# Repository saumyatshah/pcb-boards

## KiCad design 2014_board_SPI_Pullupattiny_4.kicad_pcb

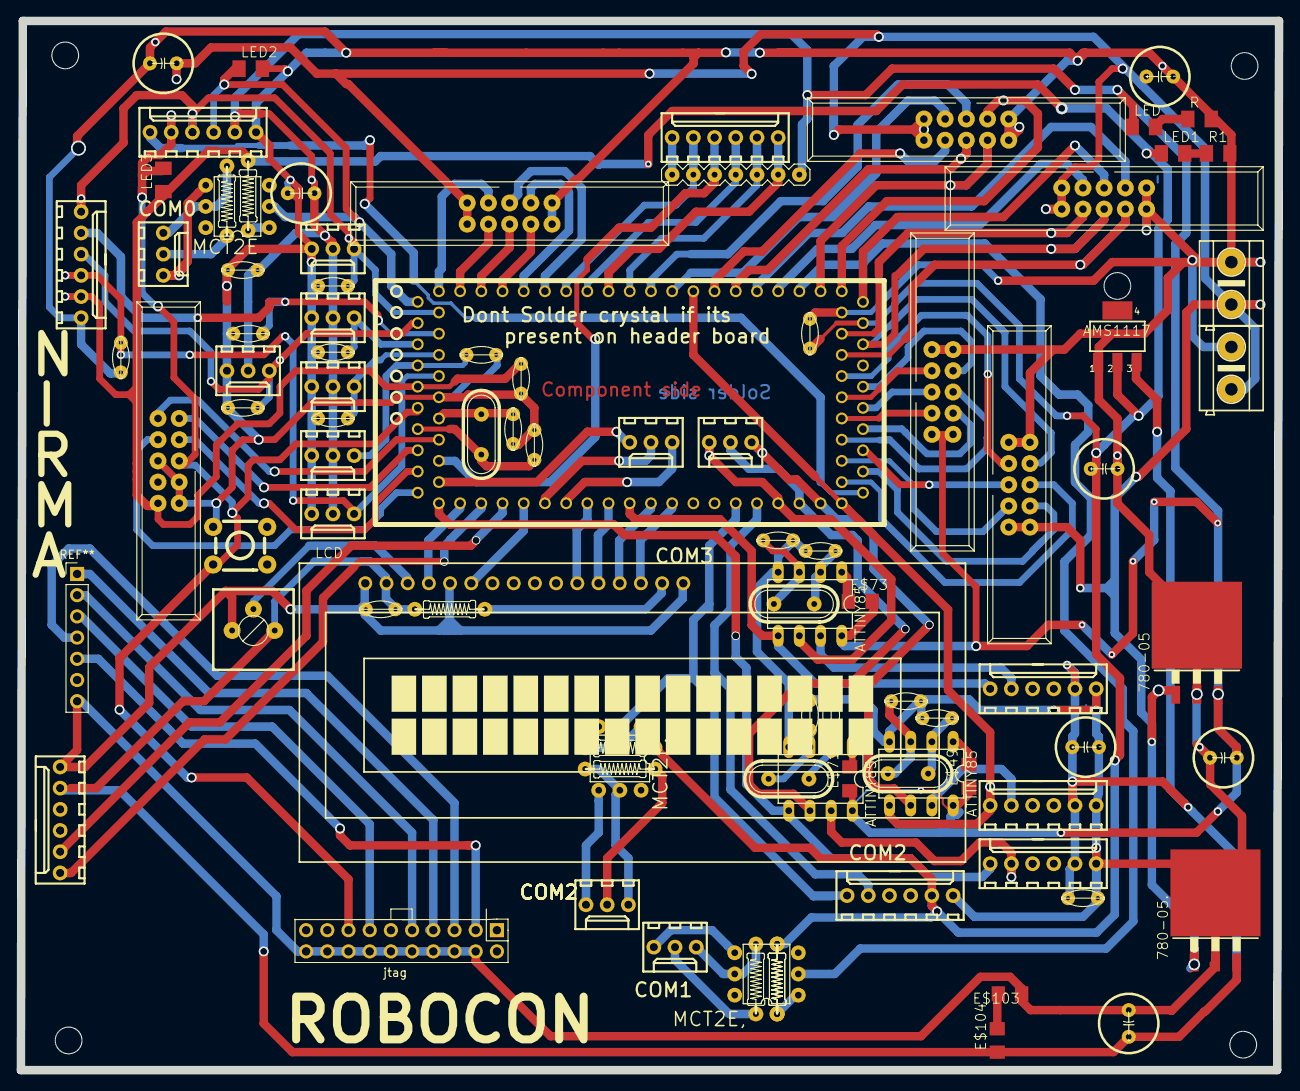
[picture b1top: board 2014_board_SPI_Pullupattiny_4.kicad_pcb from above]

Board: 2 copper layers, 150.7 x 125.7 mm, 97 parts (0 on the bottom side), 78 nets.

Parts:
780-05, 780-05.: TO263-3
@HOLE0, @HOLE1, @HOLE2, @HOLE3, @HOLE4: (no value)
AMS1117: SOT223
ATTINY85, ATTINY85,, ATTINY85.: DIL08
E$1: LPC1769-HEADER
E$2, E$18, E$27, E$30: CRYSTAL
E$3, E$4, E$5, E$6, E$15, E$19, E$20, E$25, E$26, E$28, E$29, E$31, E$51, E$57, E$61, E$62, E$66, E$67, E$85, E$86: CAPACITOR(CERAMIC)
E$7, E$8, E$8#2, E$56, E$64, E$65: FRC(10)
E$9, E$35, E$48, E$50, E$52, E$53, E$54, E$55, E$59, E$60, E$76: CONNECTOR(3_PIN)
E$13, E$34, E$36, E$69, E$70, E$74, E$75, E$95: RESISTER(HORIZONTAL)
E$21, E$22, E$23, E$32, E$37, E$83, E$84, E$106: CONNECTOR(6_PIN)
E$24, E$90, E$118, E$119, E$120, E$121, E$141: CAPACITOR(ELECTROLYTE_220)
E$38: POT(SQAURE)
E$49, E$71, E$73: R1206
E$63: SWITCH(PUSH-BUTTON)
E$103, E$104: C1206
E$108, E$109: CONNECTOR(GREEN)
E$113: RESISTER_ARRAY(7)
LCD: TUXGR_16X2_R2
LED, LED1, LED2, LED3: M1206
MCT2E, MCT2E,, MCT2E.: DIL6
R, R1: M1206
jtag: PinHeader_2x10_P2.54mm_Vertical

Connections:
3.3V: E$1.P$15, E$1.P$77, E$32.2, E$34.2, E$56.5, E$74.2, E$83.2, E$95.2, LED3.1
5V_PERIPHERALS: 780-05..3, E$13.1, E$15.2, E$21.2, E$22.2, E$23.2, E$37.2, E$37.7, E$37.8, E$37.13, E$38.3, E$104.1, E$121.+, LCD.2
5V_SHARP: ATTINY85.8, ATTINY85,.8, ATTINY85..8, E$8#2.1, E$8#2.10, E$49.1, E$50.2, E$52.2, E$53.2, E$54.2, E$55.2, E$59.2, E$71.1, E$73.2, E$84.2, E$113.7, E$120.+
12V: 780-05.1, 780-05..1, E$7.1, E$7.10, E$8.1, E$8.10, E$64.1, E$64.10, E$65.1, E$65.10, E$108.P$2, E$109.P$2, E$118.+, E$141.+
GND: 780-05.2, 780-05.TAB, 780-05..2, 780-05..TAB, AMS1117.1, ATTINY85.4, ATTINY85,.4, ATTINY85..4, E$1.P$1, E$1.P$40, E$3.1, E$4.2, E$5.1, E$6.2, E$7.5, E$7.6, E$8.5, E$8.6, E$8#2.5, E$8#2.6, E$15.1, E$19.1, E$20.2, E$21.1, E$22.1, E$23.1, E$24.-, E$25.2, E$26.1, E$28.2, E$29.2, E$31.1, E$32.1, E$37.1, E$38.1, E$50.1, E$52.1, E$53.1, E$54.1, E$55.1, E$56.3, E$56.6, E$56.7, E$57.1, E$59.1, E$63.SW1_, E$64.5, E$64.6, E$65.5, E$65.6, E$66.1, E$67.1, E$83.1, E$84.1, E$85.1, E$86.1, E$90.-, E$103.1, E$108.P$1, E$109.P$1, E$118.-, E$119.-, E$120.-, E$121.-, E$141.-, LCD.1, LCD.5, LCD.16, LED2.2, R.2, R1.2, jtag.4, jtag.6, jtag.8, jtag.10, jtag.12, jtag.14, jtag.16, jtag.18, jtag.20
S$2: ATTINY85..7, E$23.5
S$6: E$1.P$44, E$8#2.7
S$8: ATTINY85,.6, E$1.P$52, E$9.1
S$9: E$1.P$36, E$64.9
S$10: E$1.P$74, E$8#2.4
S$13: E$1.P$48, E$7.3
S$17: E$1.P$47, E$7.9
S$19: E$1.P$73, E$8#2.8
S$21: E$1.P$42, E$64.4
S$22: E$1.P$45, E$8#2.9
S$24: E$1.P$71, E$7.8
S$25: E$1.P$41, E$64.2
S$27: E$1.P$70, E$7.2
S$34: ATTINY85.5, E$1.P$32, E$1.P$49, E$22.6
S$36: E$35.2, E$36.2
S$41: E$76.3, MCT2E,.P$2
S$44: E$1.P$5, E$55.3, E$83.6, E$84.4
S$48: ATTINY85.7, E$22.5, E$22.11, E$22.17
S$51: ATTINY85,.7, E$21.5
S$52: ATTINY85..6, E$1.P$51, E$9.2
S$53: ATTINY85..5, E$1.P$68, E$23.6
S$54: ATTINY85.6, E$1.P$50, E$9.3
S$55: E$1.P$66, E$37.6, E$37.12, E$37.18
S$57: E$1.P$53, E$32.5
S$60: E$1.P$20, E$8.P$20
S$61: E$34.1, MCT2E..P$4
S$62: ATTINY85,.5, E$1.P$59, E$21.6
S$65: E$1.P$9, E$48.1
S$68: E$1.P$27, E$106.3, E$113.4
S$71: E$35.1, MCT2E..P$3
S$74: E$35.3, E$36.1, MCT2E..P$2
S$75: E$1.P$11, E$56.2
S$76: E$1.P$29, E$106.2, E$113.5
S$83: E$1.P$62, E$48.3
S$86: E$1.P$63, E$48.2
S$88: E$1.P$4, E$83.5
S$91: E$1.P$34, E$65.3
S$100: E$1.P$54, E$32.6, MCT2E..P$5
S$105: E$1.P$2, E$50.3, E$83.3
S$107: E$1.P$65, E$37.5, E$37.11, E$37.17
S$110: E$1.P$18, E$59.3, E$83.4
S$112: E$1.P$21, E$8.P$21
S$113: E$1.P$16, E$52.3
S$116: E$60.1, MCT2E.P$3
S$118: E$1.P$7, E$56.1
S$121: E$1.P$12, E$56.10
S$122: E$1.P$10, E$56.9
S$123: E$1.P$17, E$54.3
S$124: E$1.P$3, E$53.3
S$126: E$60.3, MCT2E.P$2
S$128: E$1.P$23, E$8.P$23
S$129: E$1.P$22, E$8.P$22
S$130: E$1.P$19, E$84.3, MCT2E.P$5
S$134: E$76.1, MCT2E,.P$3
S$135: E$1.P$37, MCT2E,.P$5
S$137: E$75.1, E$76.2
S$140: E$1.P$14, E$56.8, E$63.SW1, E$84.5, E$84.11, E$84.17, LED3.2, jtag.15
S$142: E$1.P$24, E$8.P$24
S$143: E$1.P$25, E$8.P$25
S$156: E$1.P$64, LCD.6
S$161: E$1.P$76, E$64.3
S$163: E$1.P$39, E$65.7
S$164: E$1.P$38, E$65.4
S$165: E$1.P$33, E$65.2
S$166: E$1.P$35, E$64.7
S$168: E$1.P$31, E$65.9
S$169: E$1.P$30, E$65.8
S$170: E$1.P$78, E$64.8
S$171: E$1.P$8, E$106.4, E$113.3
S$177: E$1.P$69, E$84.6
S$179: E$1.P$26, E$106.5, E$113.2
S$181: E$1.P$28, E$106.1, E$113.6
S$185: E$106.6, E$113.1
